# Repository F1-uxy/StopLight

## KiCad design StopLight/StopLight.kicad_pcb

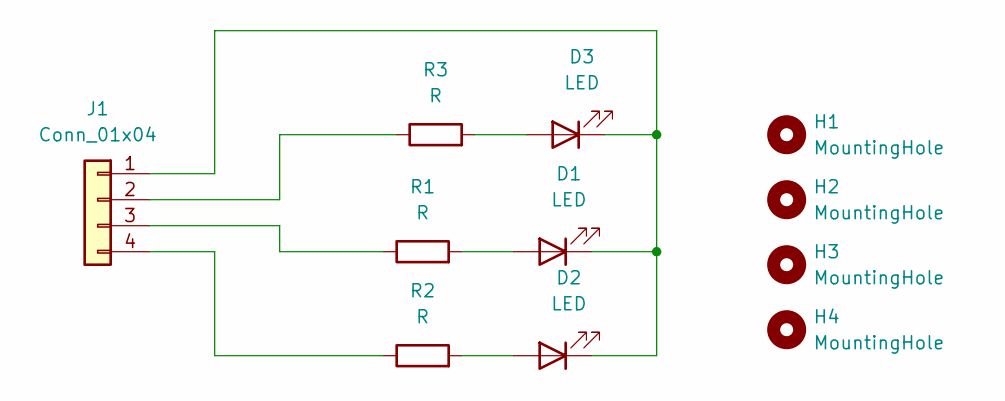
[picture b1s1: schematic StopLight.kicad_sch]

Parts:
D1, D2, D3: LED; LED_D3.0mm
H1, H2, H3, H4: MountingHole; MountingHole_2.5mm_Pad
J1: Conn_01x04; PinHeader_1x04_P2.54mm_Horizontal
R1, R2, R3: R; R_Axial_DIN0204_L3.6mm_D1.6mm_P5.08mm_Horizontal

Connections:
unnamed: D1.1 (K), D2.1 (K), D3.1 (K), J1.1
unnamed: D1.2 (A), R1.2
unnamed: D2.2 (A), R2.2
unnamed: D3.2 (A), R3.2
unnamed: J1.2, R3.1
unnamed: J1.3, R1.1
unnamed: J1.4, R2.1

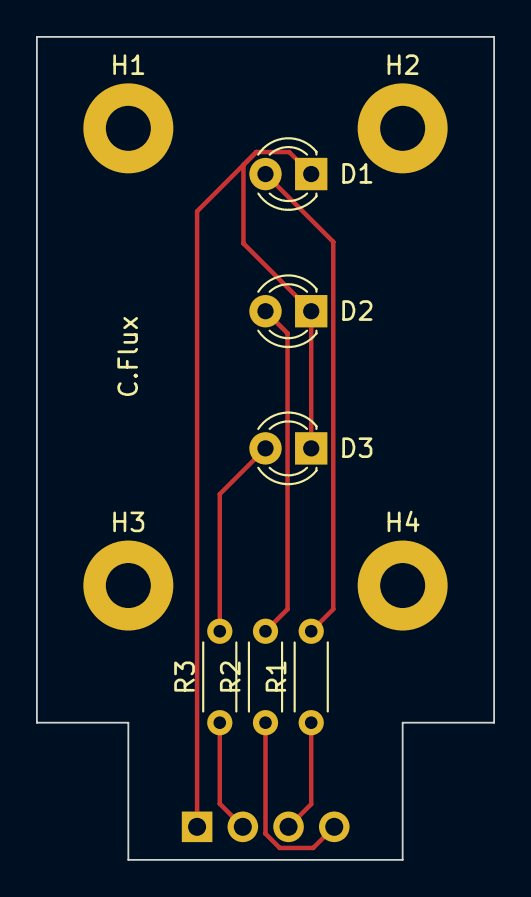
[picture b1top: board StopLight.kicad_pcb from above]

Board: 2 copper layers, 25.4 x 45.7 mm, 11 parts (1 on the bottom side), 7 nets.
